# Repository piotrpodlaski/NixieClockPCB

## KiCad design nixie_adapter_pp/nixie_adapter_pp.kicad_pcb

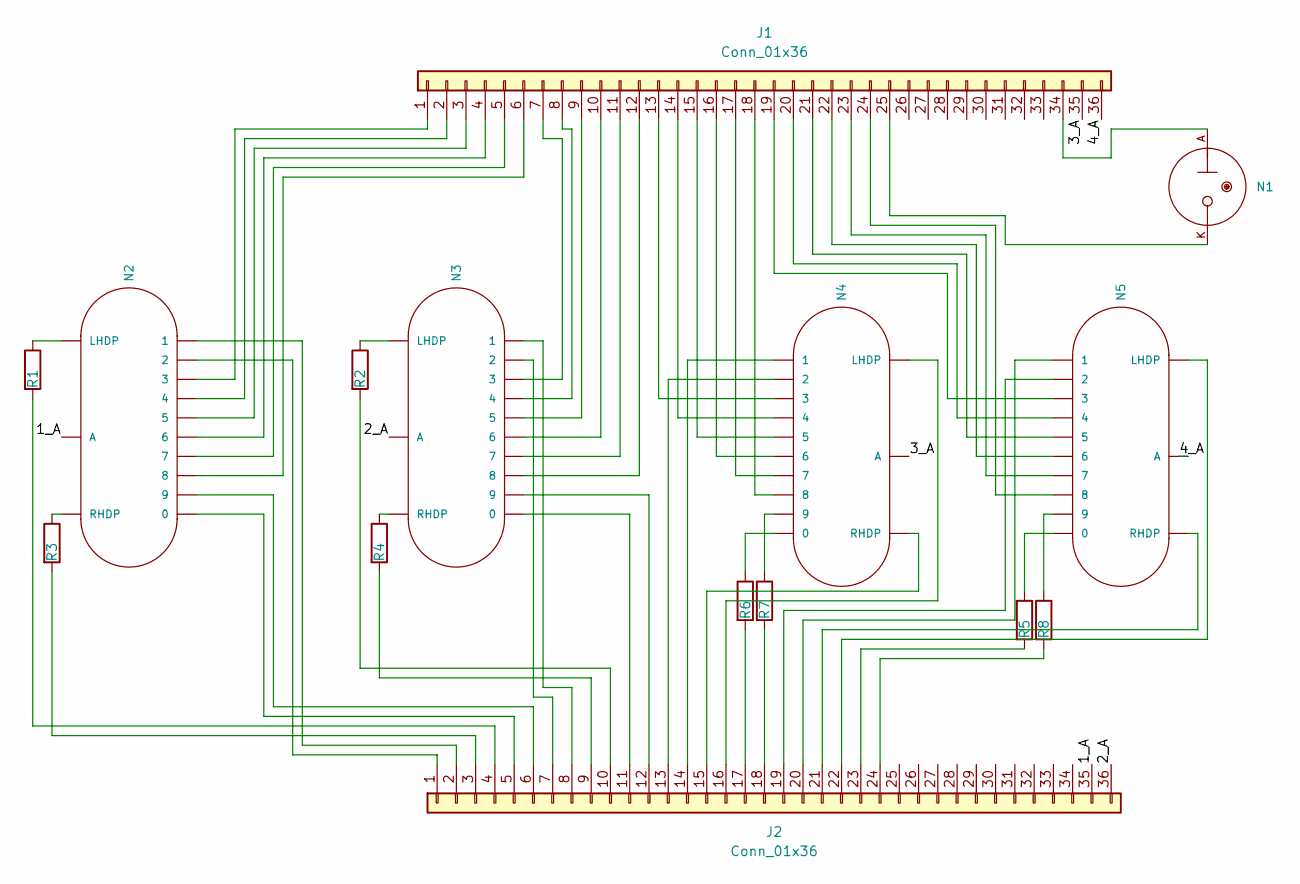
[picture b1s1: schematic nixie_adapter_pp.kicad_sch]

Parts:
J1, J2: Conn_01x36; PinHeader_1x36_P2.54mm_Vertical
N1: IN-3; nixies-us-IN-3
N2, N3, N4, N5: IN-14; nixies-us-IN-14
R1, R2, R3, R4, R5, R6, R7, R8: R; R_0805_2012Metric_Pad1.20x1.40mm_HandSolder

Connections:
/1_A: J2.35, N2.A
/2_A: J2.36, N3.A
/3_A: J1.35, N4.A
/4_A: J1.36, N5.A
unnamed: J1.1, N2.8 (3)
unnamed: J1.2, N2.7 (4)
unnamed: J1.3, N2.6 (5)
unnamed: J1.4, N2.5 (6)
unnamed: J1.5, N2.4 (7)
unnamed: J1.6, N2.3 (8)
unnamed: J1.7, N3.8 (3)
unnamed: J1.8, N3.7 (4)
unnamed: J1.9, N3.6 (5)
unnamed: J1.10, N3.5 (6)
unnamed: J1.13, N4.8 (3)
unnamed: J1.14, N4.7 (4)
unnamed: J1.15, N4.6 (5)
unnamed: J1.16, N4.5 (6)
unnamed: J1.17, N4.4 (7)
unnamed: J1.18, N4.3 (8)
unnamed: J1.19, N5.8 (3)
unnamed: J1.20, N5.7 (4)
unnamed: J1.21, N5.6 (5)
unnamed: J1.22, N5.5 (6)
unnamed: J1.23, N5.4 (7)
unnamed: J1.24, N5.3 (8)
unnamed: J1.25, N1.K
unnamed: J1.34, N1.A
unnamed: J2.1, N2.9 (2)
unnamed: J2.2, N2.0 (1)
unnamed: J2.3, R3.2
unnamed: J2.4, R1.2
unnamed: J2.5, N2.1 (0)
unnamed: J2.6, N2.2 (9)
unnamed: J2.7, N3.9 (2)
unnamed: J2.9, R4.2
unnamed: J2.10, R2.2
unnamed: J2.13, N4.9 (2)
unnamed: J2.14, N4.0 (1)
unnamed: J2.15, N4.RHDP
unnamed: J2.16, N4.LHDP
unnamed: J2.17, R6.2
unnamed: J2.18, R7.2
unnamed: J2.19, N5.9 (2)
unnamed: J2.20, N5.0 (1)
unnamed: J2.21, N5.RHDP
unnamed: J2.23, R5.2
unnamed: J2.24, R8.2
unnamed: N2.LHDP, R1.1
unnamed: N2.RHDP, R3.1
unnamed: J2.8, N3.0 (1)
unnamed: J2.11, N3.1 (0)
unnamed: J2.12, N3.2 (9)
unnamed: J1.12, N3.3 (8)
unnamed: J1.11, N3.4 (7)
unnamed: N3.LHDP, R2.1
unnamed: N3.RHDP, R4.1
unnamed: N4.1 (0), R6.1
unnamed: N4.2 (9), R7.1
unnamed: N5.2 (9), R8.1
unnamed: J2.22, N5.LHDP
unnamed: N5.1 (0), R5.1

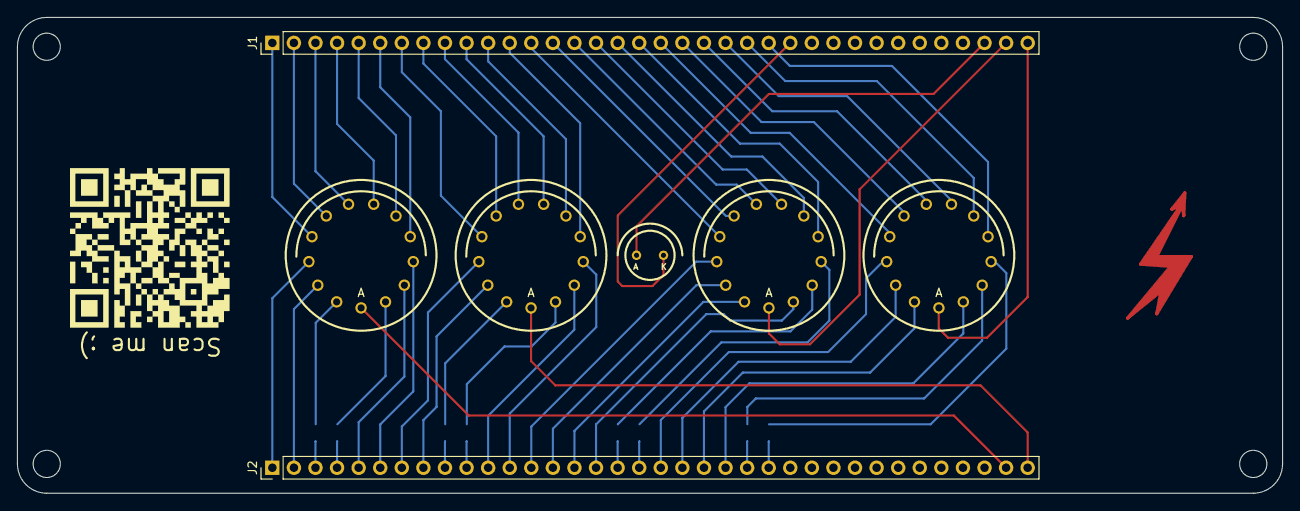
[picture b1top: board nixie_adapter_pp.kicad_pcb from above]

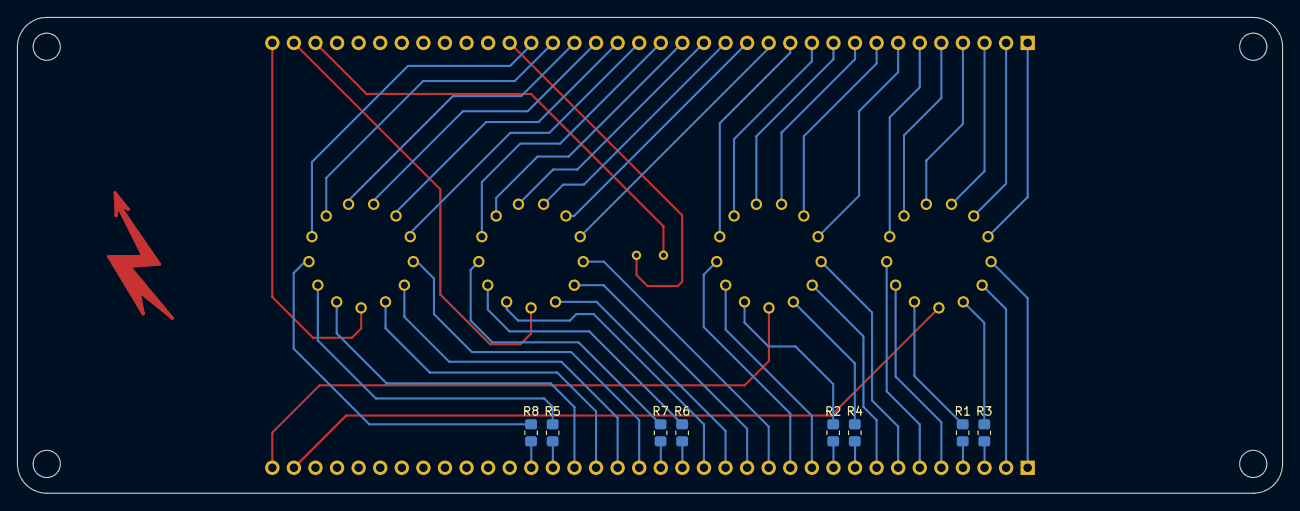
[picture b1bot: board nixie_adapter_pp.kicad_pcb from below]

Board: 2 copper layers, 148.9 x 56.0 mm, 19 parts (8 on the bottom side), 62 nets.

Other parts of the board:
H1, H2, H3, H4: MountingHole; MountingHole_3.2mm_M3

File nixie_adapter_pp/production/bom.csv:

Designator,Footprint,Quantity,Value,LCSC Part #
"H1, H2, H3, H4",MountingHole_3.2mm_M3,4,MountingHole,
"J1, J2",PinHeader_1x36_P2.54mm_Vertical,2,Conn_01x36,
N1,nixies-us-IN-3,1,IN-3,
"N2, N3, N4, N5",nixies-us-IN-14,4,IN-14,
R1,0805,1,R,
R2,0805,1,R,
R3,0805,1,R,
R4,0805,1,R,
R5,0805,1,R,
R6,0805,1,R,
R7,0805,1,R,
R8,0805,1,R,

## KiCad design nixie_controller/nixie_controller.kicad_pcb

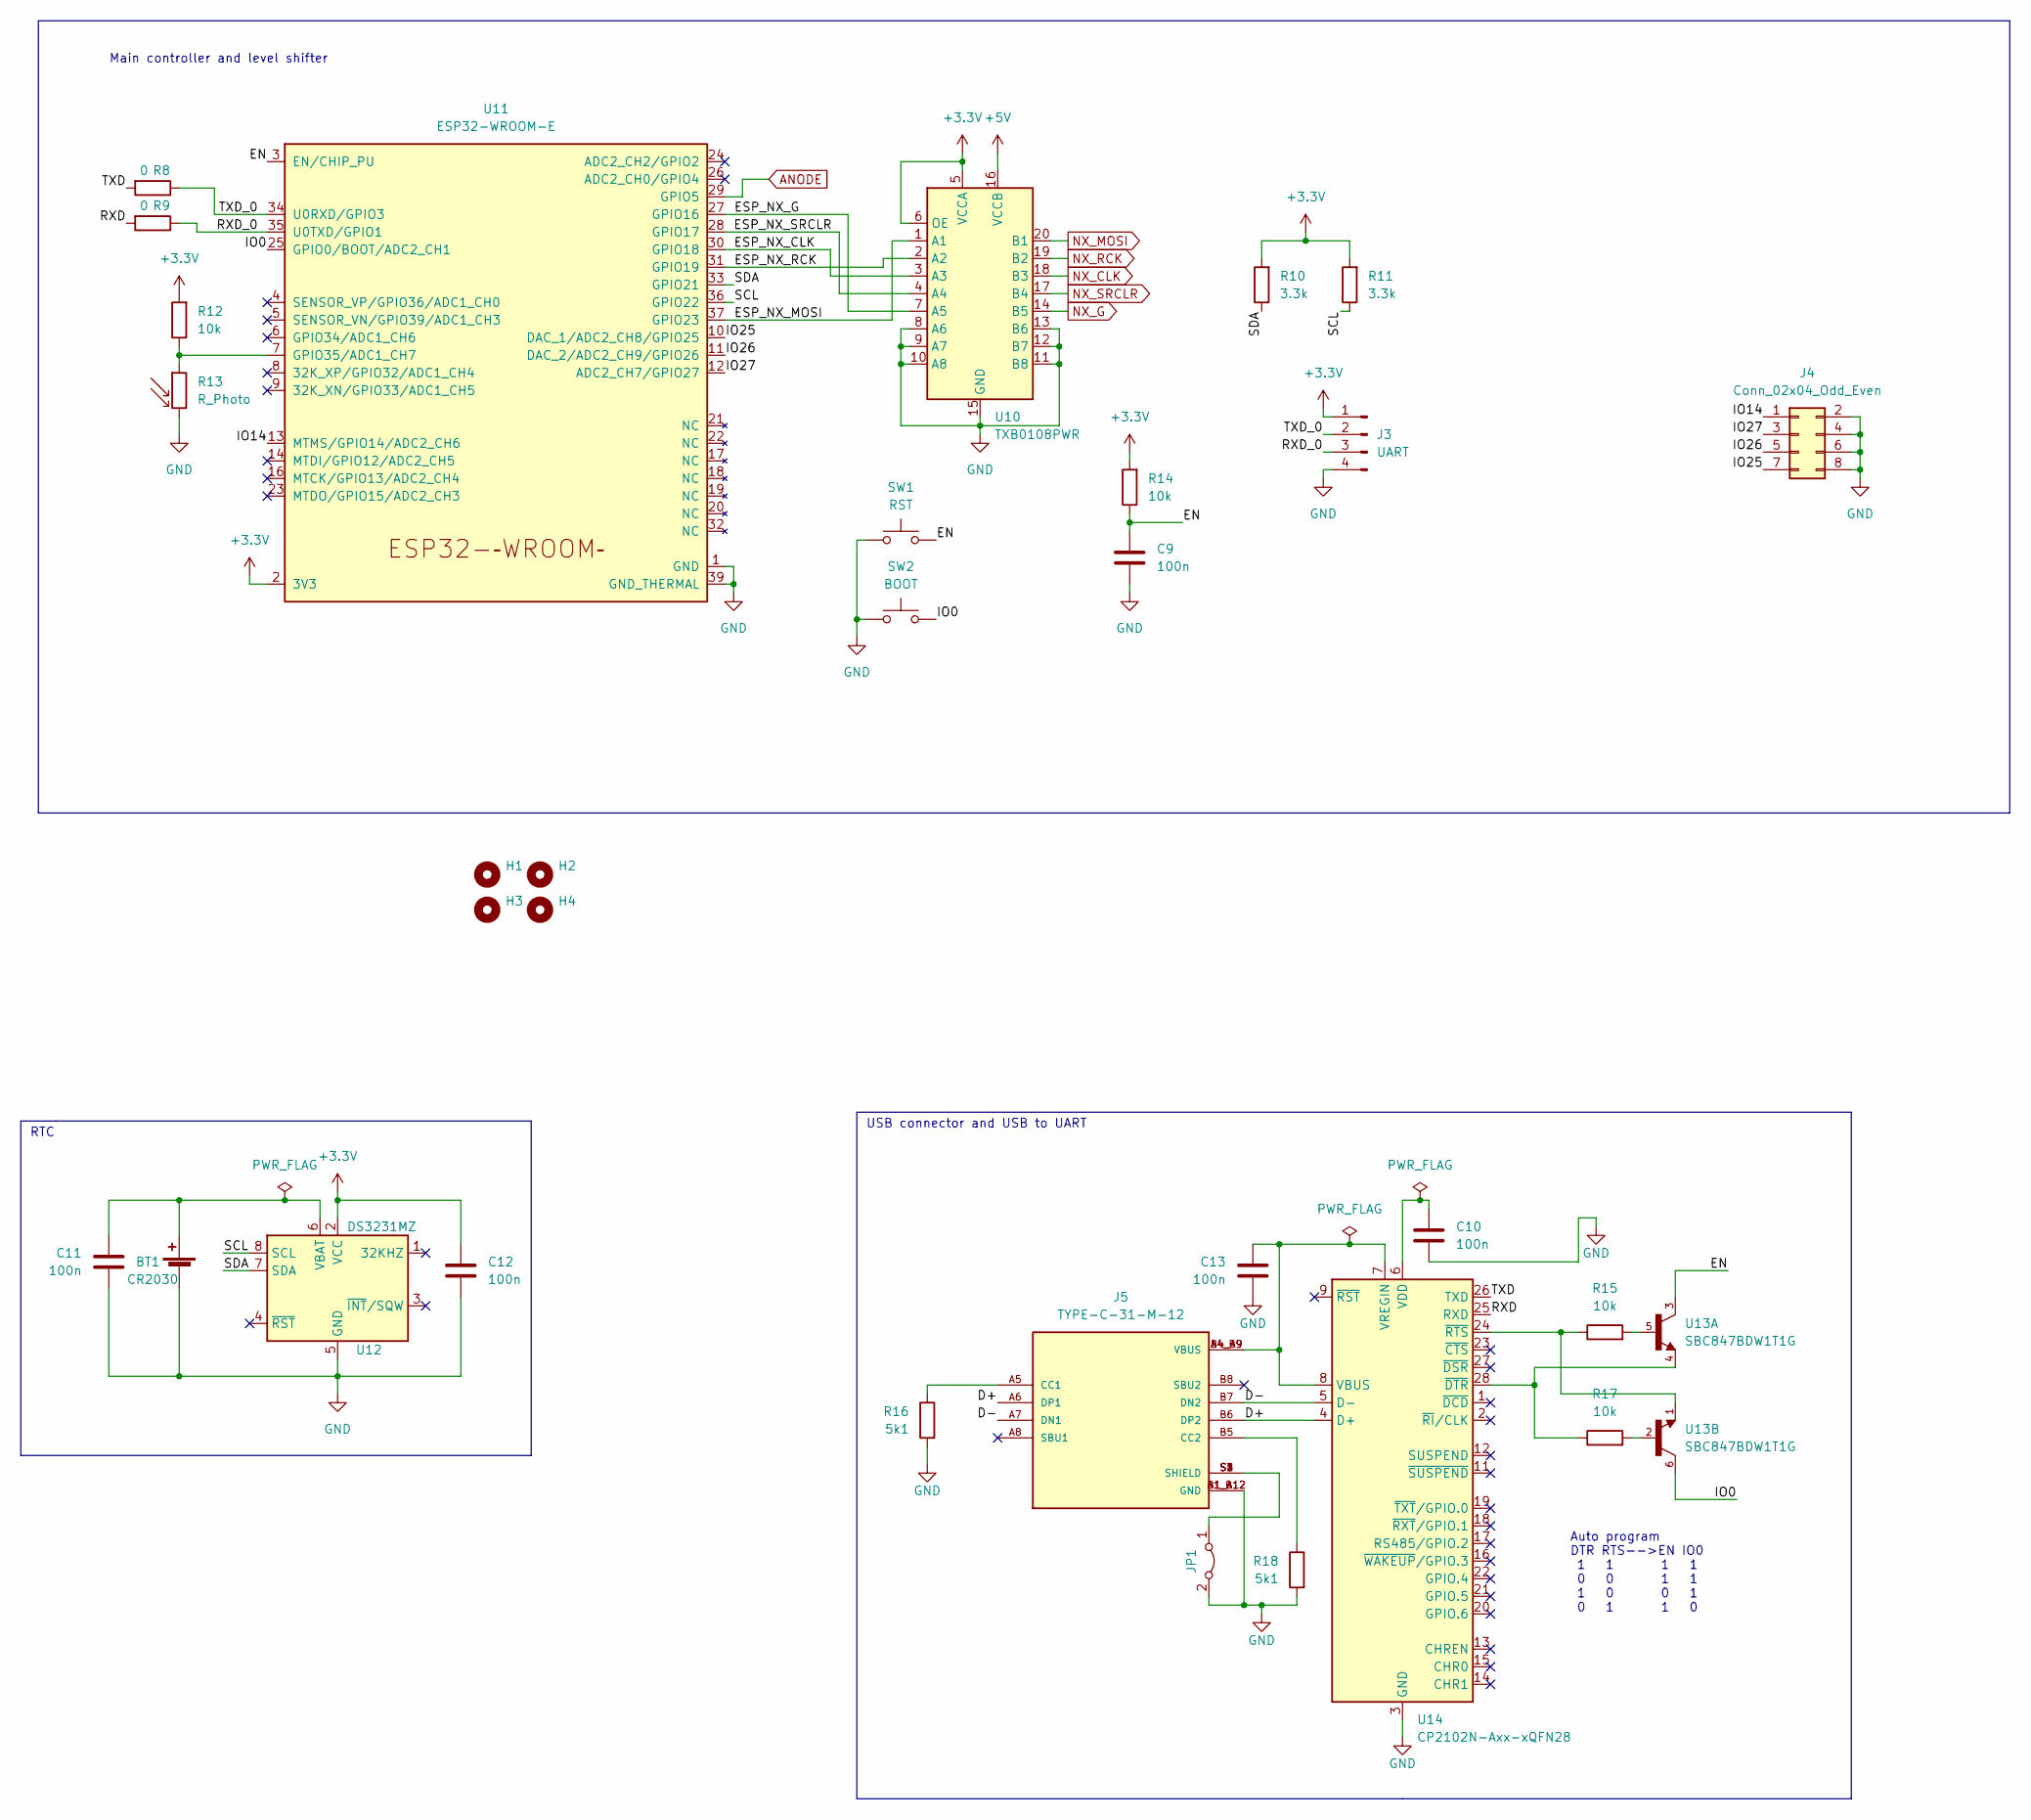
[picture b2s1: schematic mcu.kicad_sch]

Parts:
BT1: CR2030; BatteryHolder_Keystone_1060_1x2032; LCSC C238069
C9, C10, C11, C12, C13: 100n; C_0805_2012Metric_Pad1.18x1.45mm_HandSolder; LCSC C396718
H1, H2, H3, H4: MountingHole; MountingHole_3.2mm_M3; LCSC NOPLACE
J3: UART; PinHeader_1x04_P2.54mm_Vertical; LCSC NOPLACE
J4: Conn_02x04_Odd_Even; PinHeader_2x04_P2.00mm_Vertical_SMD; LCSC NOPLACE
J5: TYPE-C-31-M-12; HRO_TYPE-C-31-M-12; PARTREV 2020.12.08; LCSC C165948
JP1: Jumper_2_Bridged; SolderJumper-2_P1.3mm_Bridged_Pad1.0x1.5mm; LCSC NOPLACE
R8, R9: 0; R_0805_2012Metric_Pad1.20x1.40mm_HandSolder; LCSC C17477
R10, R11: 3.3k; R_0805_2012Metric_Pad1.20x1.40mm_HandSolder; LCSC C26010
R12, R14, R15, R17: 10k; R_0805_2012Metric_Pad1.20x1.40mm_HandSolder; LCSC C17414
R13: R_Photo; PinSocket_1x02_P2.54mm_Vertical; LCSC C125627
R16, R18: 5k1; R_0805_2012Metric_Pad1.20x1.40mm_HandSolder; LCSC C269748
SW1: RST; SW_Push_SPST_NO_Alps_SKRK; LCSC C202388
SW2: BOOT; SW_Push_SPST_NO_Alps_SKRK; LCSC C202388
U10: TXB0108PWR; TSSOP-20_4.4x6.5mm_P0.65mm; LCSC C53406
U11: ESP32-WROOM-E; ESP32-WROOM-32E; LCSC C473012
U12: DS3231MZ; SOIC-8_3.9x4.9mm_P1.27mm; LCSC C107410
U13: SBC847BDW1T1G; SOT65P210X110-6N; LCSC C232475
U14: CP2102N-Axx-xQFN28; QFN-28-1EP_5x5mm_P0.5mm_EP3.35x3.35mm; LCSC C6568

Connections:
+5V: U10.16 (VCCB); also elsewhere on the board
/MCU/D+: J5.A6 (DP1), J5.B6 (DP2), U14.4 (D+)
/MCU/D-: J5.A7 (DN1), J5.B7 (DN2), U14.5 (D-)
/MCU/EN: C9.2, R14.1, SW1.2, U11.3 (EN/CHIP_PU), U13.3
/MCU/ESP_NX_CLK: U10.3 (A3), U11.30 (GPIO18)
/MCU/ESP_NX_G: U10.7 (A5), U11.27 (GPIO16)
/MCU/ESP_NX_MOSI: U10.1 (A1), U11.37 (GPIO23)
/MCU/ESP_NX_RCK: U10.2 (A2), U11.31 (GPIO19)
/MCU/ESP_NX_SRCLR: U10.4 (A4), U11.28 (GPIO17)
/MCU/IO0: SW2.2, U11.25 (GPIO0/BOOT/ADC2_CH1), U13.6
/MCU/IO25: J4.7, U11.10 (DAC_1/ADC2_CH8/GPIO25); also elsewhere on the board
/MCU/IO26: J4.5, U11.11 (DAC_2/ADC2_CH9/GPIO26); also elsewhere on the board
/MCU/RXD: R9.2, U14.25 (RXD)
/MCU/RXD_0: J3.3, R9.1, U11.35 (U0TXD/GPIO1)
/MCU/TXD: R8.2, U14.26 (TXD)
/MCU/TXD_0: J3.2, R8.1, U11.34 (U0RXD/GPIO3)
ANODE: U11.29 (GPIO5); also elsewhere on the board
NX_CLK: U10.18 (B3); also elsewhere on the board
NX_G: U10.14 (B5); also elsewhere on the board
NX_MOSI: U10.20 (B1); also elsewhere on the board
NX_RCK: U10.19 (B2); also elsewhere on the board
NX_SRCLR: U10.17 (B4); also elsewhere on the board
unnamed: BT1.1 (+), C11.2, U12.6 (VBAT)
unnamed: C10.2, U14.6 (VDD)
unnamed: C13.2, J5.A4_B9 (VBUS), J5.B4_A9 (VBUS), U14.7 (VREGIN), U14.8 (VBUS)
unnamed: J5.A5 (CC1), R16.1
unnamed: J5.B5 (CC2), R18.1
unnamed: J5.S1 (SHIELD), J5.S2 (SHIELD), J5.S3 (SHIELD), J5.S4 (SHIELD), JP1.1 (A)
unnamed: R12.1, R13.1, U11.7 (GPIO35/ADC1_CH7)
unnamed: R15.1, U13.1, U14.24 (~RTS)
unnamed: R15.2, U13.5
unnamed: R17.1, U13.4, U14.28 (~DTR)
unnamed: R17.2, U13.2

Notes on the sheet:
Auto program DTR RTS-->EN IO0 1 1 1 1 0 0 1 1 1 0 0 1 0 1 1 0
Main controller and level shifter
RTC
USB connector and USB to UART

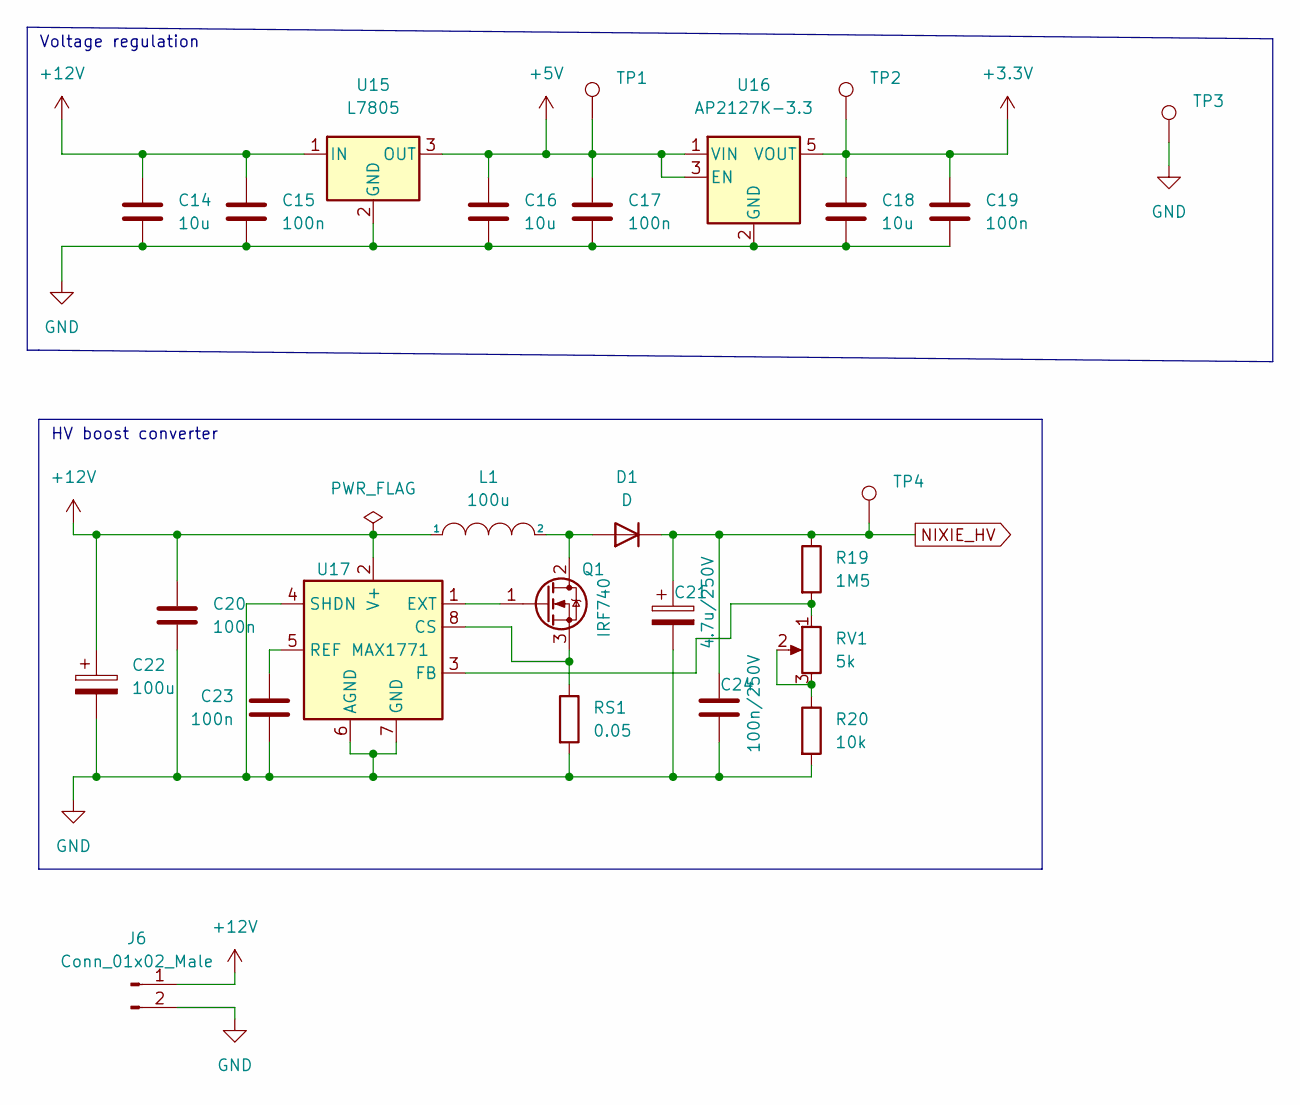
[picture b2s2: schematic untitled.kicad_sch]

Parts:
C14, C16, C18: 10u; C_0805_2012Metric_Pad1.18x1.45mm_HandSolder; LCSC C1713
C15, C17, C19, C20, C23: 100n; C_0805_2012Metric_Pad1.18x1.45mm_HandSolder; LCSC C396718
C21: 4.7u/250V; C_Elec_8x10.2; LCSC C88702
C22: 100u; CP_EIA-7343-15_Kemet-W; LCSC C122302
C24: 100n/250V; C_1210_3225Metric; LCSC C52020
D1: D; D_SMB; LCSC C145321
J6: Conn_01x02_Male; PinSocket_1x02_P2.54mm_Vertical; LCSC NOPLACE
L1: 100u; L_10.4x10.4_H4.8; LCSC C2962892
Q1: IRF740; TO-263-2; LCSC C39238
R19: 1M5; R_0805_2012Metric_Pad1.20x1.40mm_HandSolder; LCSC C137463
R20: 10k; R_0805_2012Metric_Pad1.20x1.40mm_HandSolder; LCSC C17414
RS1: 0.05; R_1206_3216Metric_Pad1.30x1.75mm_HandSolder; LCSC C149662
RV1: 5k; Potentiometer_Bourns_3296P_Horizontal; LCSC C780227
TP1: 5V0; TestPoint_Pad_1.5x1.5mm; LCSC NOPLACE
TP2: 3V3; TestPoint_Pad_1.5x1.5mm; LCSC NOPLACE
TP3: GND; TestPoint_Pad_1.5x1.5mm; LCSC NOPLACE
TP4: HV; TestPoint_Pad_1.5x1.5mm; LCSC NOPLACE
U15: L7805; TO-252-2; LCSC C310413
U16: AP2127K-3.3; SOT-23-5; LCSC C156285
U17: MAX1771; SO-8_5.3x6.2mm_P1.27mm; LCSC C407903

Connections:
+5V: C16.2, C17.2, TP1.1, U15.3 (OUT), U16.1 (VIN), U16.3 (EN); also elsewhere on the board
+12V: C14.2, C15.2, C20.1, C22.1, J6.1, L1.1, U15.1 (IN), U17.2 (V+)
NIXIE_HV: C21.1, C24.1, D1.1 (K), R19.1, TP4.1; also elsewhere on the board
unnamed: C23.2, U17.5 (REF)
unnamed: D1.2 (A), L1.2, Q1.2 (D)
unnamed: Q1.1 (G), U17.1 (EXT)
unnamed: Q1.3 (S), RS1.1, U17.8 (CS)
unnamed: R19.2, RV1.1, U17.3 (FB)
unnamed: R20.1, RV1.2, RV1.3

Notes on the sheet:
Voltage regulation
HV boost converter

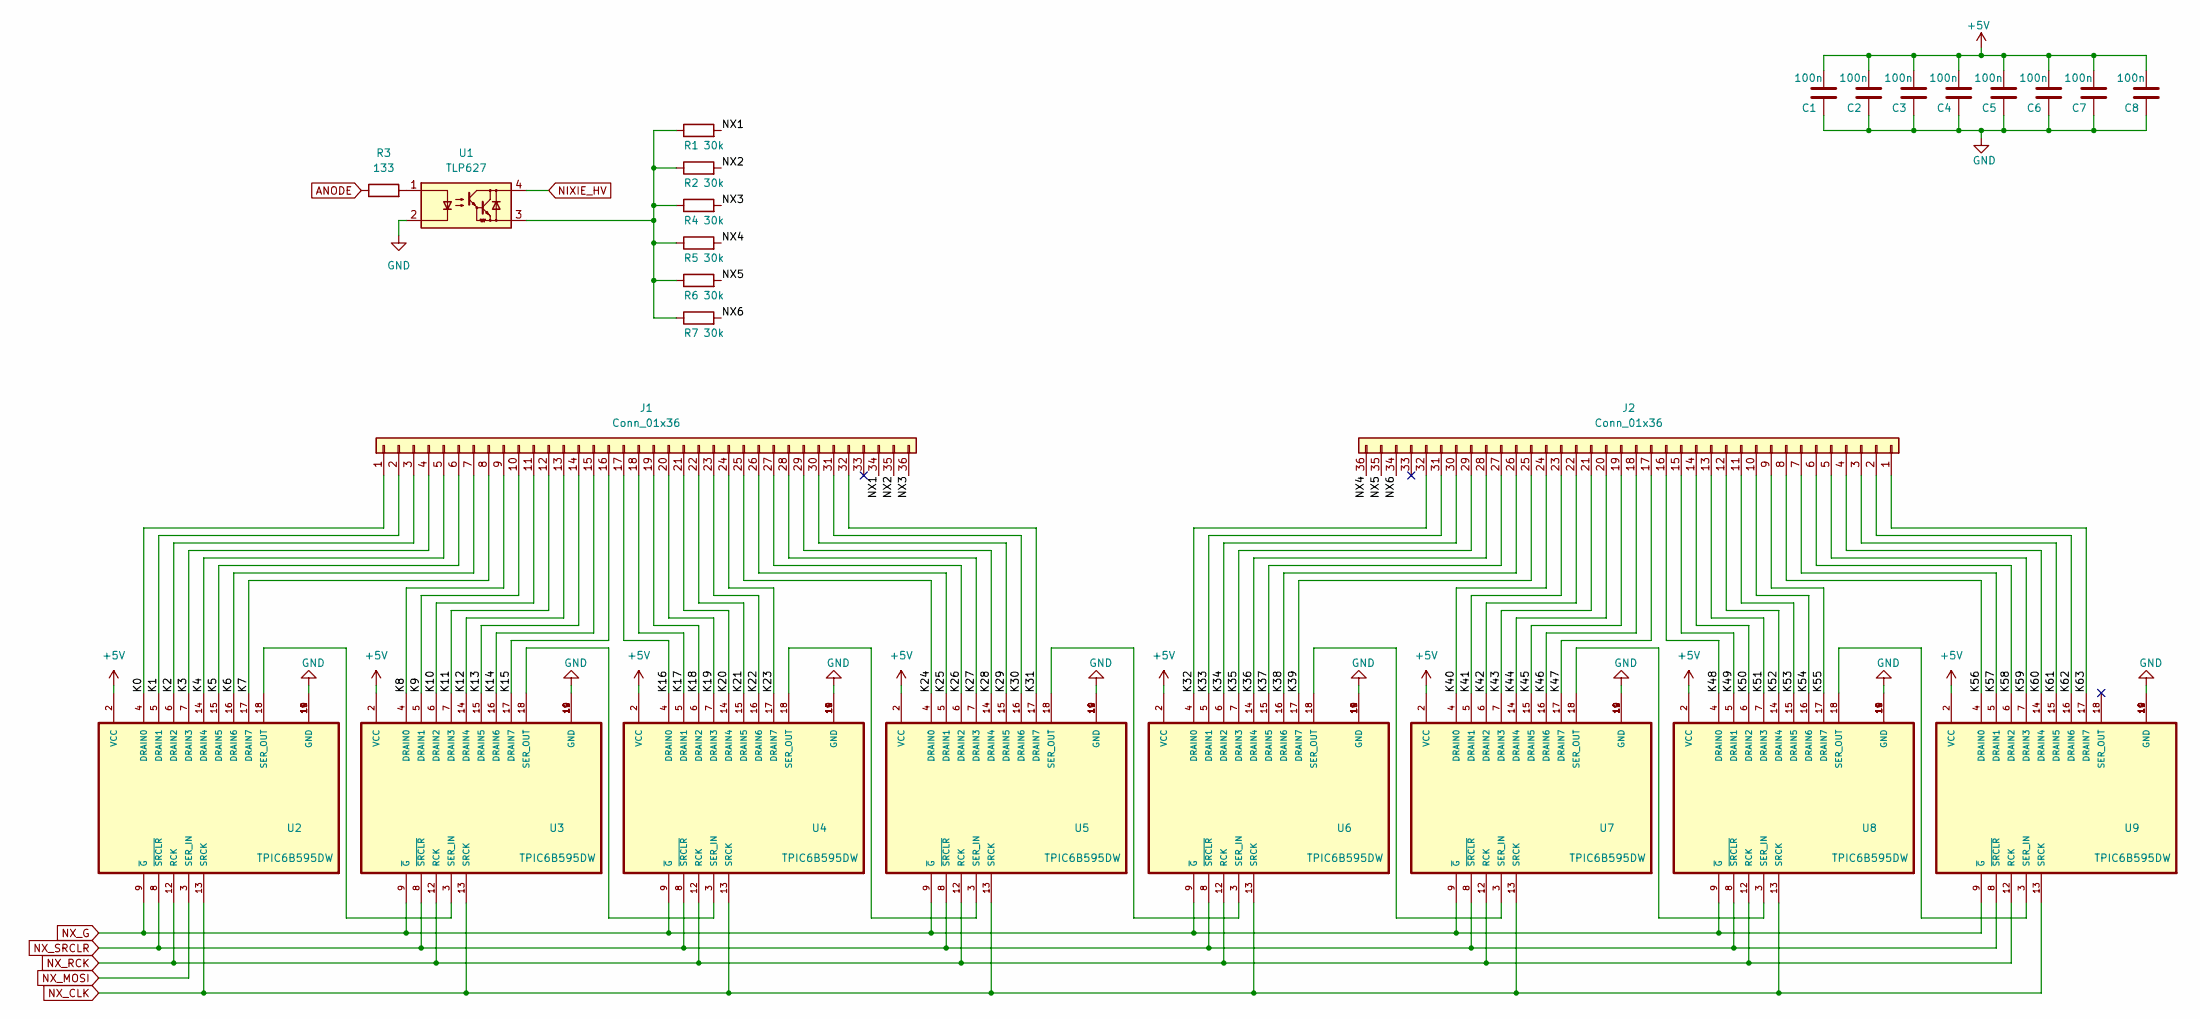
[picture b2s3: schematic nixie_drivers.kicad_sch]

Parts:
C1, C2, C3, C4, C5, C6, C7, C8: 100n; C_0805_2012Metric_Pad1.18x1.45mm_HandSolder; LCSC C396718
J1: Conn_01x36; PinSocket_1x36_P2.54mm_Vertical; LCSC NOPLACE
J2: Conn_01x36; PinHeader_1x36_P2.54mm_Vertical; LCSC NOPLACE
R1, R2, R4, R5, R6, R7: 30k; R_0805_2012Metric_Pad1.20x1.40mm_HandSolder; LCSC C17621
R3: 133; R_0805_2012Metric_Pad1.20x1.40mm_HandSolder; LCSC C2828762
U1: TLP627; SOP-4_3.8x4.1mm_P2.54mm; LCSC C30336
U2, U3, U4, U5, U6, U7, U8, U9: TPIC6B595DW; SOIC127P1030X265-20N; LCSC C7094

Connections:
+5V: C1.2, C2.2, C3.2, C4.2, C5.2, C6.2, C7.2, C8.2, U2.2 (VCC), U3.2 (VCC), U4.2 (VCC), U5.2 (VCC), U6.2 (VCC), U7.2 (VCC), U8.2 (VCC), U9.2 (VCC); also elsewhere on the board
/nixie_drivers/K0: J1.1, U2.4 (DRAIN0)
/nixie_drivers/K1: J1.2, U2.5 (DRAIN1)
/nixie_drivers/K2: J1.3, U2.6 (DRAIN2)
/nixie_drivers/K3: J1.4, U2.7 (DRAIN3)
/nixie_drivers/K4: J1.5, U2.14 (DRAIN4)
/nixie_drivers/K5: J1.6, U2.15 (DRAIN5)
/nixie_drivers/K6: J1.7, U2.16 (DRAIN6)
/nixie_drivers/K7: J1.8, U2.17 (DRAIN7)
/nixie_drivers/K8: J1.9, U3.4 (DRAIN0)
/nixie_drivers/K9: J1.10, U3.5 (DRAIN1)
/nixie_drivers/K10: J1.11, U3.6 (DRAIN2)
/nixie_drivers/K11: J1.12, U3.7 (DRAIN3)
/nixie_drivers/K12: J1.13, U3.14 (DRAIN4)
/nixie_drivers/K13: J1.14, U3.15 (DRAIN5)
/nixie_drivers/K14: J1.15, U3.16 (DRAIN6)
/nixie_drivers/K15: J1.16, U3.17 (DRAIN7)
/nixie_drivers/K16: J1.17, U4.4 (DRAIN0)
/nixie_drivers/K17: J1.18, U4.5 (DRAIN1)
/nixie_drivers/K18: J1.19, U4.6 (DRAIN2)
/nixie_drivers/K19: J1.20, U4.7 (DRAIN3)
/nixie_drivers/K20: J1.21, U4.14 (DRAIN4)
/nixie_drivers/K21: J1.22, U4.15 (DRAIN5)
/nixie_drivers/K22: J1.23, U4.16 (DRAIN6)
/nixie_drivers/K23: J1.24, U4.17 (DRAIN7)
/nixie_drivers/K24: J1.25, U5.4 (DRAIN0)
/nixie_drivers/K25: J1.26, U5.5 (DRAIN1)
/nixie_drivers/K26: J1.27, U5.6 (DRAIN2)
/nixie_drivers/K27: J1.28, U5.7 (DRAIN3)
/nixie_drivers/K28: J1.29, U5.14 (DRAIN4)
/nixie_drivers/K29: J1.30, U5.15 (DRAIN5)
/nixie_drivers/K30: J1.31, U5.16 (DRAIN6)
/nixie_drivers/K31: J1.32, U5.17 (DRAIN7)
/nixie_drivers/K32: J2.32, U6.4 (DRAIN0)
/nixie_drivers/K33: J2.31, U6.5 (DRAIN1)
/nixie_drivers/K34: J2.30, U6.6 (DRAIN2)
/nixie_drivers/K35: J2.29, U6.7 (DRAIN3)
/nixie_drivers/K36: J2.28, U6.14 (DRAIN4)
/nixie_drivers/K37: J2.27, U6.15 (DRAIN5)
/nixie_drivers/K38: J2.26, U6.16 (DRAIN6)
/nixie_drivers/K39: J2.25, U6.17 (DRAIN7)
/nixie_drivers/K40: J2.24, U7.4 (DRAIN0)
/nixie_drivers/K41: J2.23, U7.5 (DRAIN1)
/nixie_drivers/K42: J2.22, U7.6 (DRAIN2)
/nixie_drivers/K43: J2.21, U7.7 (DRAIN3)
/nixie_drivers/K44: J2.20, U7.14 (DRAIN4)
/nixie_drivers/K45: J2.19, U7.15 (DRAIN5)
/nixie_drivers/K46: J2.18, U7.16 (DRAIN6)
/nixie_drivers/K47: J2.17, U7.17 (DRAIN7)
/nixie_drivers/K48: J2.16, U8.4 (DRAIN0)
/nixie_drivers/K49: J2.15, U8.5 (DRAIN1)
/nixie_drivers/K50: J2.14, U8.6 (DRAIN2)
/nixie_drivers/K51: J2.13, U8.7 (DRAIN3)
/nixie_drivers/K52: J2.12, U8.14 (DRAIN4)
/nixie_drivers/K53: J2.11, U8.15 (DRAIN5)
/nixie_drivers/K54: J2.10, U8.16 (DRAIN6)
/nixie_drivers/K55: J2.9, U8.17 (DRAIN7)
/nixie_drivers/K56: J2.8, U9.4 (DRAIN0)
/nixie_drivers/K57: J2.7, U9.5 (DRAIN1)
/nixie_drivers/K58: J2.6, U9.6 (DRAIN2)
/nixie_drivers/K59: J2.5, U9.7 (DRAIN3)
/nixie_drivers/K60: J2.4, U9.14 (DRAIN4)
/nixie_drivers/K61: J2.3, U9.15 (DRAIN5)
/nixie_drivers/K62: J2.2, U9.16 (DRAIN6)
/nixie_drivers/K63: J2.1, U9.17 (DRAIN7)
/nixie_drivers/NX1: J1.34, R1.2
/nixie_drivers/NX2: J1.35, R2.2
/nixie_drivers/NX3: J1.36, R4.2
/nixie_drivers/NX4: J2.36, R5.2
/nixie_drivers/NX5: J2.35, R6.2
/nixie_drivers/NX6: J2.34, R7.2
ANODE: R3.1; also elsewhere on the board
NIXIE_HV: U1.4; also elsewhere on the board
NX_CLK: U2.13 (SRCK), U3.13 (SRCK), U4.13 (SRCK), U5.13 (SRCK), U6.13 (SRCK), U7.13 (SRCK), U8.13 (SRCK), U9.13 (SRCK); also elsewhere on the board
NX_G: U2.9 (~G), U3.9 (~G), U4.9 (~G), U5.9 (~G), U6.9 (~G), U7.9 (~G), U8.9 (~G), U9.9 (~G); also elsewhere on the board
NX_MOSI: U2.3 (SER_IN); also elsewhere on the board
NX_RCK: U2.12 (RCK), U3.12 (RCK), U4.12 (RCK), U5.12 (RCK), U6.12 (RCK), U7.12 (RCK), U8.12 (RCK), U9.12 (RCK); also elsewhere on the board
NX_SRCLR: U2.8 (~SRCLR), U3.8 (~SRCLR), U4.8 (~SRCLR), U5.8 (~SRCLR), U6.8 (~SRCLR), U7.8 (~SRCLR), U8.8 (~SRCLR), U9.8 (~SRCLR); also elsewhere on the board
unnamed: R1.1, R2.1, R4.1, R5.1, R6.1, R7.1, U1.3
unnamed: R3.2, U1.1
unnamed: U2.18 (SER_OUT), U3.3 (SER_IN)
unnamed: U3.18 (SER_OUT), U4.3 (SER_IN)
unnamed: U4.18 (SER_OUT), U5.3 (SER_IN)
unnamed: U5.18 (SER_OUT), U6.3 (SER_IN)
unnamed: U6.18 (SER_OUT), U7.3 (SER_IN)
unnamed: U7.18 (SER_OUT), U8.3 (SER_IN)
unnamed: U8.18 (SER_OUT), U9.3 (SER_IN)

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
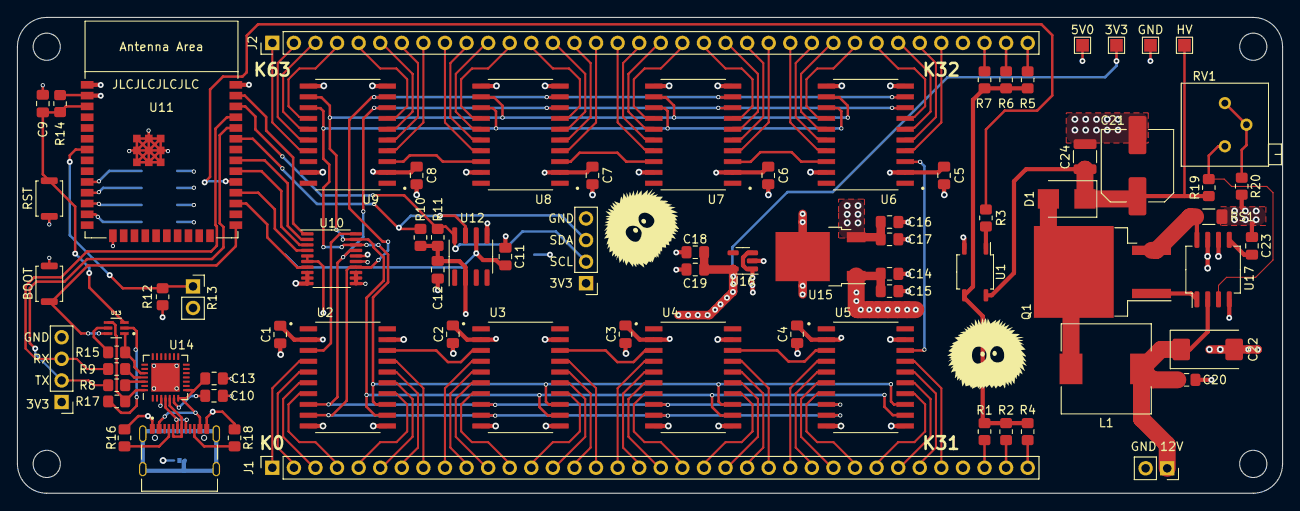
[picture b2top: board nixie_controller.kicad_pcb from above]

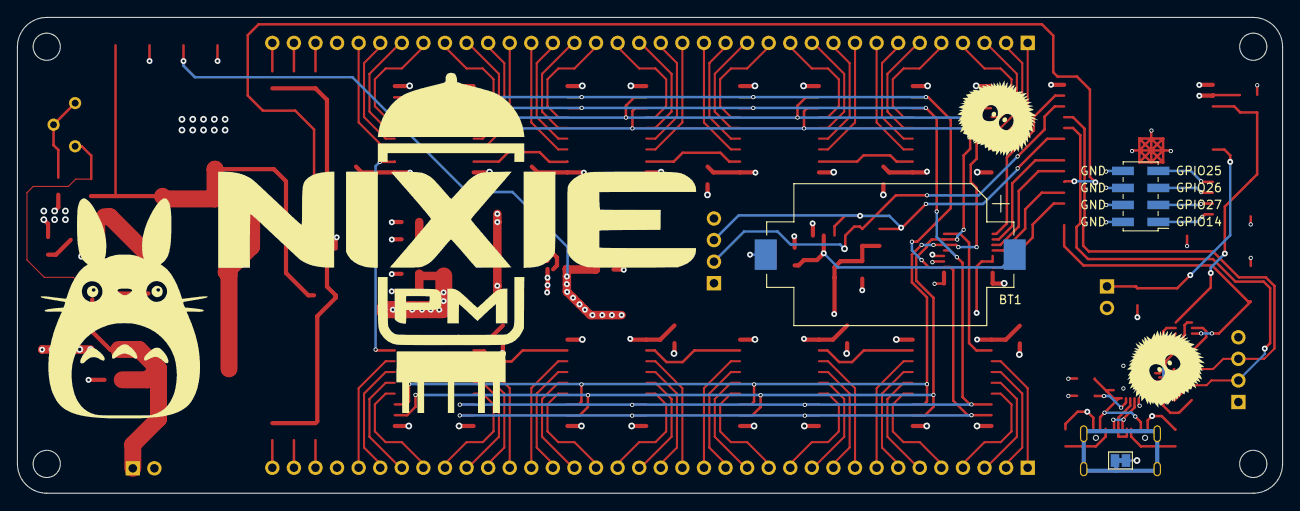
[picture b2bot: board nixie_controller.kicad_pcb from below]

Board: 4 copper layers, 148.9 x 56.0 mm, 85 parts (3 on the bottom side), 126 nets.

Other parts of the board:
J4#2: Conn_02x04_Odd_Even; PinHeader_2x04_P2.00mm_Vertical_SMD

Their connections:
/MCU/IO25: J4#2.7; also elsewhere on the board
/MCU/IO26: J4#2.5; also elsewhere on the board

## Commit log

2023-03-22 remove unnecessary 3d
2023-03-22 expose pdfs
2023-03-22 add bom
2023-07-25 level conveter fix
